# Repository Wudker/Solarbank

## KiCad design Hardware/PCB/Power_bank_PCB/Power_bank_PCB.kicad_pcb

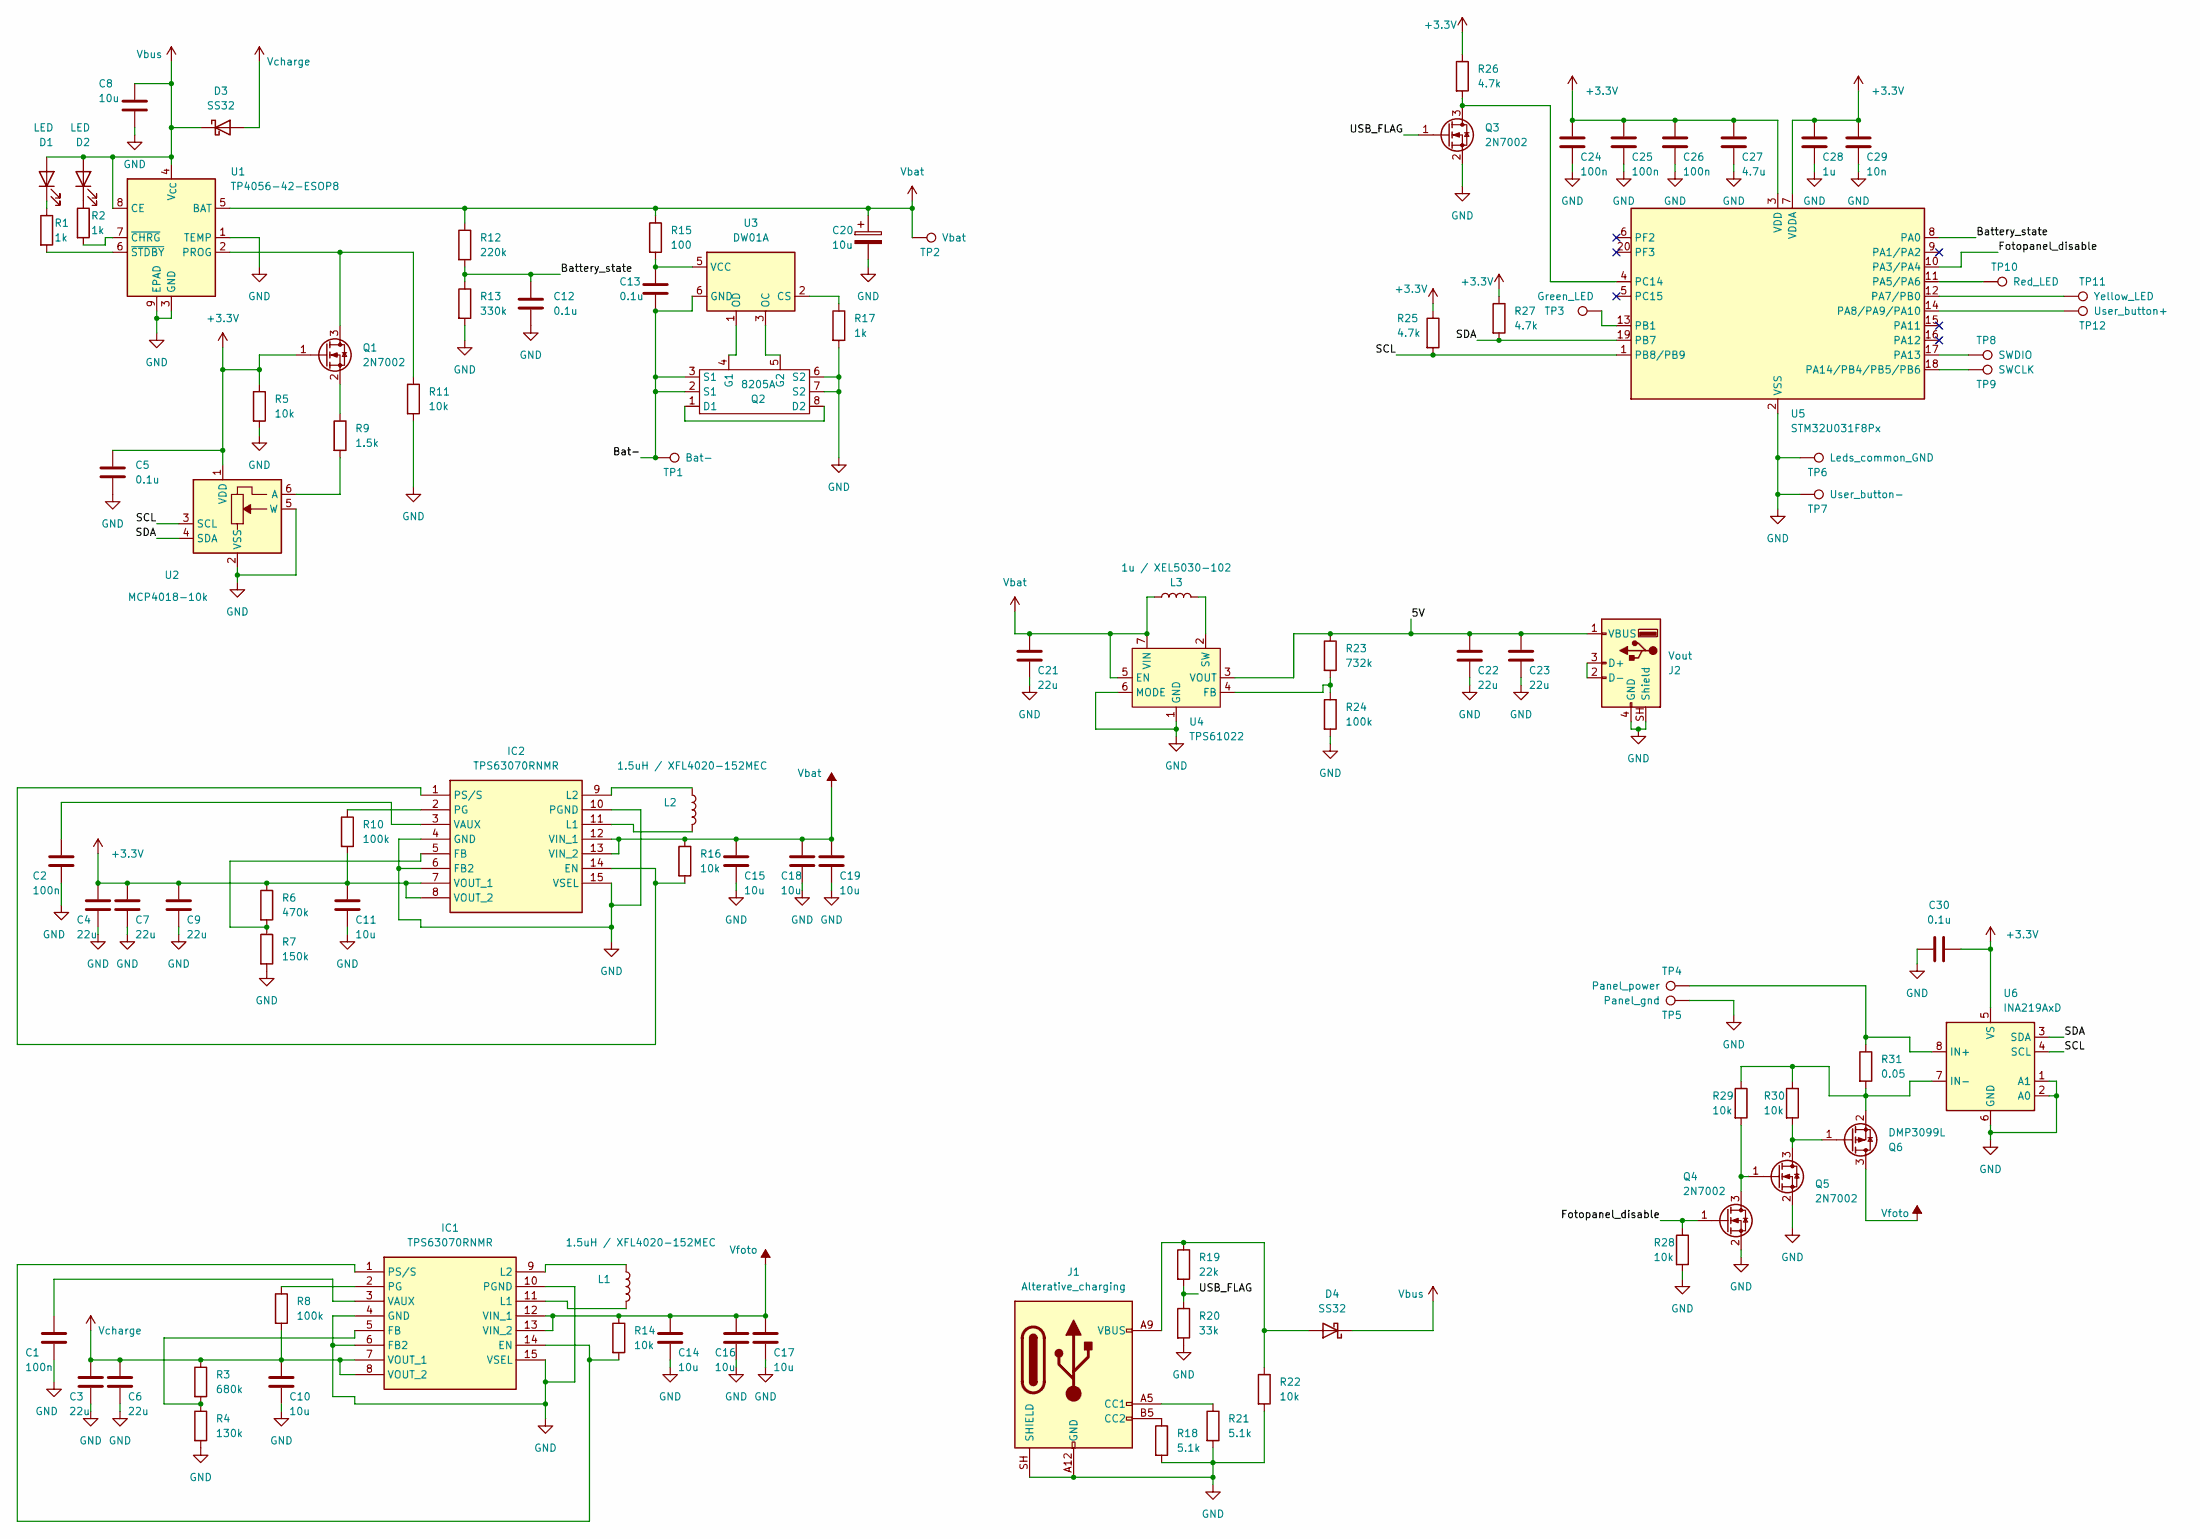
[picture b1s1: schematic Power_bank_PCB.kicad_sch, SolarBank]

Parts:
C1, C2, C24, C25, C26: 100n; C_1206_3216Metric
C3, C4, C6, C7, C9, C21, C22, C23: 22u; C_1206_3216Metric
C5, C12, C13, C30: 0.1u; C_1206_3216Metric
C8, C10, C11, C14, C15, C16, C17, C18, C19, C20: 10u; C_1206_3216Metric
C27: 4.7u; C_1206_3216Metric
C28: 1u; C_1206_3216Metric
C29: 10n; C_1206_3216Metric
D1, D2: LED; LED_1206_3216Metric_Pad1.42x1.75mm_HandSolder
D3, D4: SS32; D_SMA
IC1, IC2: TPS63070RNMR; TPS630701RNMR; Manufacturer_Part_Number TPS63070RNMR
J1: Alterative_charging; USB_C_Receptacle_GCT_USB4125-xx-x-0190_6P_TopMnt_Horizontal
J2: Vout; USB_A_Molex_67643_Horizontal
L1, L2: 1.5uH / XFL4020-152MEC; L_Coilcraft_XAL4020-XXX
L3: 1u / XEL5030-102; L_Coilcraft_XAL5030-XXX
Q1, Q3, Q4, Q5: 2N7002; SOT-23
Q2: 8205A; TSSOP-8_4.4x3mm_P0.65mm
Q6: DMP3099L; SOT-23
R1, R2, R17: 1k; R_1206_3216Metric
R3: 680k; R_1206_3216Metric
R4: 130k; R_1206_3216Metric
R5, R11, R14, R16, R22, R28, R29, R30: 10k; R_1206_3216Metric
R6: 470k; R_1206_3216Metric
R7: 150k; R_1206_3216Metric
R8, R10, R24: 100k; R_1206_3216Metric
R9: 1.5k; R_1206_3216Metric
R12: 220k; R_1206_3216Metric
R13: 330k; R_1206_3216Metric
R15: 100; R_1206_3216Metric
R18, R21: 5.1k; R_1206_3216Metric
R19: 22k; R_1206_3216Metric
R20: 33k; R_1206_3216Metric
R23: 732k; R_1206_3216Metric
R25, R26, R27: 4.7k; R_1206_3216Metric
R31: 0.05; R_1206_3216Metric
TP1: Bat-; TestPoint_Pad_D2.0mm
TP2: Vbat; TestPoint_Pad_D2.0mm
TP3: Green_LED; TestPoint_Pad_D2.0mm
TP4: Panel_power; TestPoint_Pad_D2.0mm
TP5: Panel_gnd; TestPoint_Pad_D2.0mm
TP6: Leds_common_GND; TestPoint_Pad_D2.0mm
TP7: User_button-; TestPoint_Pad_D2.0mm
TP8: SWDIO; TestPoint_Pad_D2.0mm
TP9: SWCLK; TestPoint_Pad_D2.0mm
TP10: Red_LED; TestPoint_Pad_D2.0mm
TP11: Yellow_LED; TestPoint_Pad_D2.0mm
TP12: User_button+; TestPoint_Pad_D2.0mm
U1: TP4056-42-ESOP8; SOIC-8-1EP_3.9x4.9mm_P1.27mm_EP2.41x3.3mm_ThermalVias
U2: MCP4018-10k; SOT-363_SC-70-6
U3: DW01A; SOT-23-6
U4: TPS61022; Texas_RWU0007A_VQFN-7_2x2mm_P0.5mm
U5: STM32U031F8Px; TSSOP-20_4.4x6.5mm_P0.65mm
U6: INA219AxD; SOIC-8_3.9x4.9mm_P1.27mm

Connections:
+3.3V: C4.2, C5.1, C7.2, C9.2, C11.2, C24.2, C25.2, C26.2, C27.2, C28.2, C29.2, C30.2, IC2.7 (VOUT_1), IC2.8 (VOUT_2), Q1.1 (G), R5.1, R6.1, R10.2, R25.1, R26.1, R27.1, U2.1 (VDD), U5.3 (VDD), U5.7 (VDDA), U6.5 (VS)
/5V: C22.2, C23.2, J2.1 (VBUS), R23.1, U4.3 (VOUT)
/Bat-: C13.1, Q2.2 (S1), Q2.3 (S1), TP1.1 (1_1), U3.6 (GND)
/Battery_state: C12.1, R12.2, R13.1, U5.8 (PA0)
/Fotopanel_disable: Q4.1 (G), R28.1, U5.10 (PA3/PA4)
/SCL: R25.2, U2.3 (SCL), U5.1 (PB8/PB9), U6.4 (SCL)
/SDA: R27.2, U2.4 (SDA), U5.19 (PB7), U6.3 (SDA)
/USB_FLAG: Q3.1 (G), R19.2, R20.1
GND: C1.1, C2.1, C3.1, C4.1, C5.2, C6.1, C7.1, C8.2, C9.1, C10.1, C11.1, C12.2, C14.1, C15.1, C16.1, C17.1, C18.1, C19.1, C20.2, C21.1, C22.1, C23.1, C24.1, C25.1, C26.1, C27.1, C28.1, C29.1, C30.1, IC1.4 (GND), IC1.6 (FB2), IC1.10 (PGND), IC1.15 (VSEL), IC2.4 (GND), IC2.6 (FB2), IC2.10 (PGND), IC2.15 (VSEL), J1.A12 (GND), J1.B12 (GND), J1.SH (SHIELD), J2.4 (GND), J2.SH (Shield), Q2.6 (S2), Q2.7 (S2), Q3.2 (S), Q4.2 (S), Q5.2 (S), R4.2, R5.2, R7.2, R11.2, R13.2, R17.2, R18.2, R20.2, R21.2, R22.2, R24.2, R28.2, TP5.1 (1_1), TP6.1 (1_1), TP7.1 (1_1), U1.1 (TEMP), U1.3 (GND), U1.9 (EPAD), U2.2 (VSS), U2.5 (W), U4.1 (GND), U4.6 (MODE), U5.2 (VSS), U6.1 (A1), U6.2 (A0), U6.6 (GND)
unnamed: D1.1 (K), R1.1
unnamed: D2.1 (K), R2.1
unnamed: D4.2 (A), J1.A9 (VBUS), J1.B9 (VBUS), R19.1, R22.1
unnamed: IC1.1 (PS/S), IC1.14 (EN), R14.2
unnamed: IC1.5 (FB), R3.2, R4.1
unnamed: IC1.11 (L1), L1.2
unnamed: IC1.9 (L2), L1.1
unnamed: IC1.2 (PG), R8.1
unnamed: C1.2, IC1.3 (VAUX)
unnamed: IC2.1 (PS/S), IC2.14 (EN), R16.2
unnamed: IC2.5 (FB), R6.2, R7.1
unnamed: IC2.11 (L1), L2.2
unnamed: IC2.9 (L2), L2.1
unnamed: IC2.2 (PG), R10.1
unnamed: C2.2, IC2.3 (VAUX)
unnamed: J1.A5 (CC1), R21.1
unnamed: J1.B5 (CC2), R18.1
unnamed: J2.2 (D-), J2.3 (D+)
unnamed: Q1.3 (D), R11.1, U1.2 (PROG)
unnamed: Q1.2 (S), R9.1
unnamed: Q2.1 (D1), Q2.8 (D2)
unnamed: Q2.4 (G1), U3.1 (OD)
unnamed: Q2.5 (G2), U3.3 (OC)
unnamed: Q3.3 (D), R26.2, U5.4 (PC14)
unnamed: Q4.3 (D), Q5.1 (G), R29.2
unnamed: Q5.3 (D), Q6.1 (G), R30.2
unnamed: Q6.2 (S), R29.1, R30.1, R31.2, U6.7 (IN-)
unnamed: R2.2, U1.7 (~CHRG)
unnamed: R1.2, U1.6 (~STDBY)
unnamed: R9.2, U2.6 (A)
unnamed: R17.1, U3.2 (CS)
unnamed: C13.2, R15.2, U3.5 (VCC)
unnamed: R23.2, R24.1, U4.4 (FB)
unnamed: L3.2, U4.2 (SW)
unnamed: TP10.1 (1_1), U5.11 (PA5/PA6)
unnamed: TP11.1 (1_1), U5.12 (PA7/PB0)
unnamed: TP12.1 (1_1), U5.14 (PA8/PA9/PA10)
unnamed: TP8.1 (1_1), U5.17 (PA13)
unnamed: TP9.1 (1_1), U5.18 (PA14/PB4/PB5/PB6)
unnamed: TP3.1 (1_1), U5.13 (PB1)
unnamed: R31.1, TP4.1 (1_1), U6.8 (IN+)
Vbat: C15.2, C18.2, C19.2, C20.1, C21.2, IC2.12 (VIN_1), IC2.13 (VIN_2), L3.1, R12.1, R15.1, R16.1, TP2.1 (1_1), U1.5 (BAT), U4.5 (EN), U4.7 (VIN)
Vbus: C8.1, D1.2 (A), D2.2 (A), D3.1 (K), D4.1 (K), U1.4 (V_{CC}), U1.8 (CE)
Vcharge: C3.2, C6.2, C10.2, D3.2 (A), IC1.7 (VOUT_1), IC1.8 (VOUT_2), R3.1, R8.2
Vfoto: C14.2, C16.2, C17.2, IC1.12 (VIN_1), IC1.13 (VIN_2), Q6.3 (D), R14.1

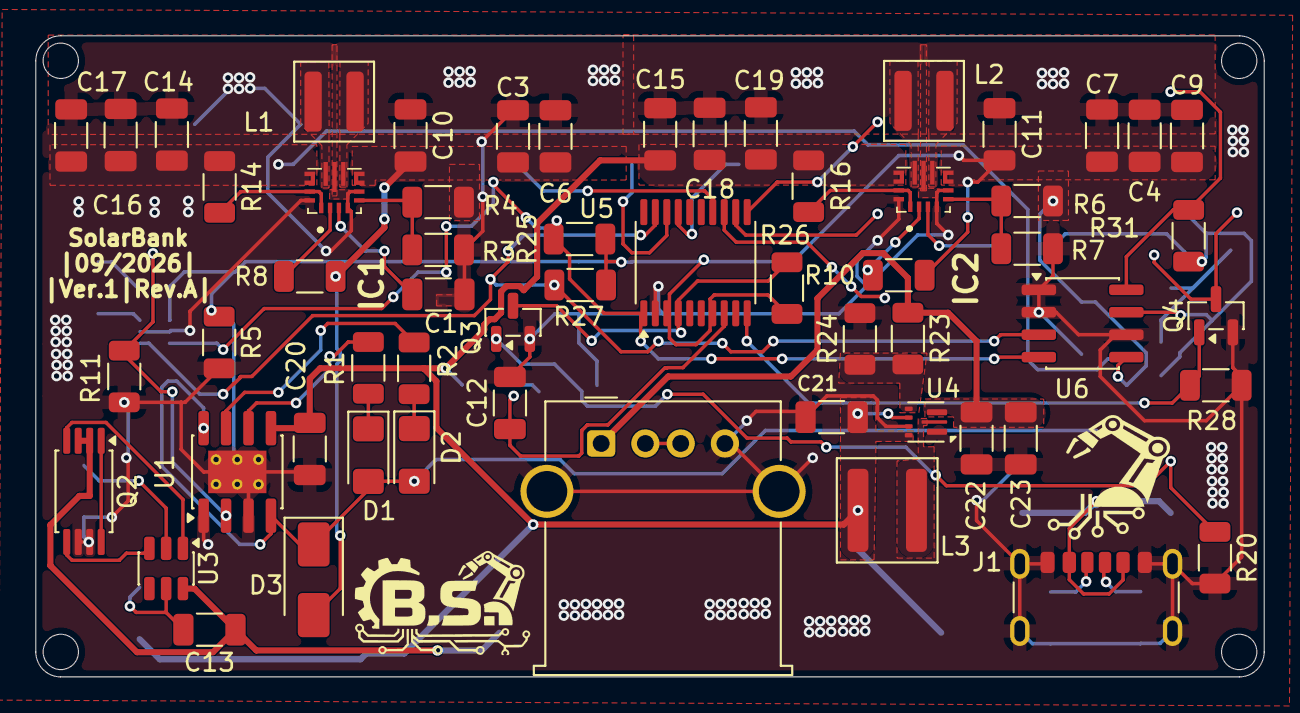
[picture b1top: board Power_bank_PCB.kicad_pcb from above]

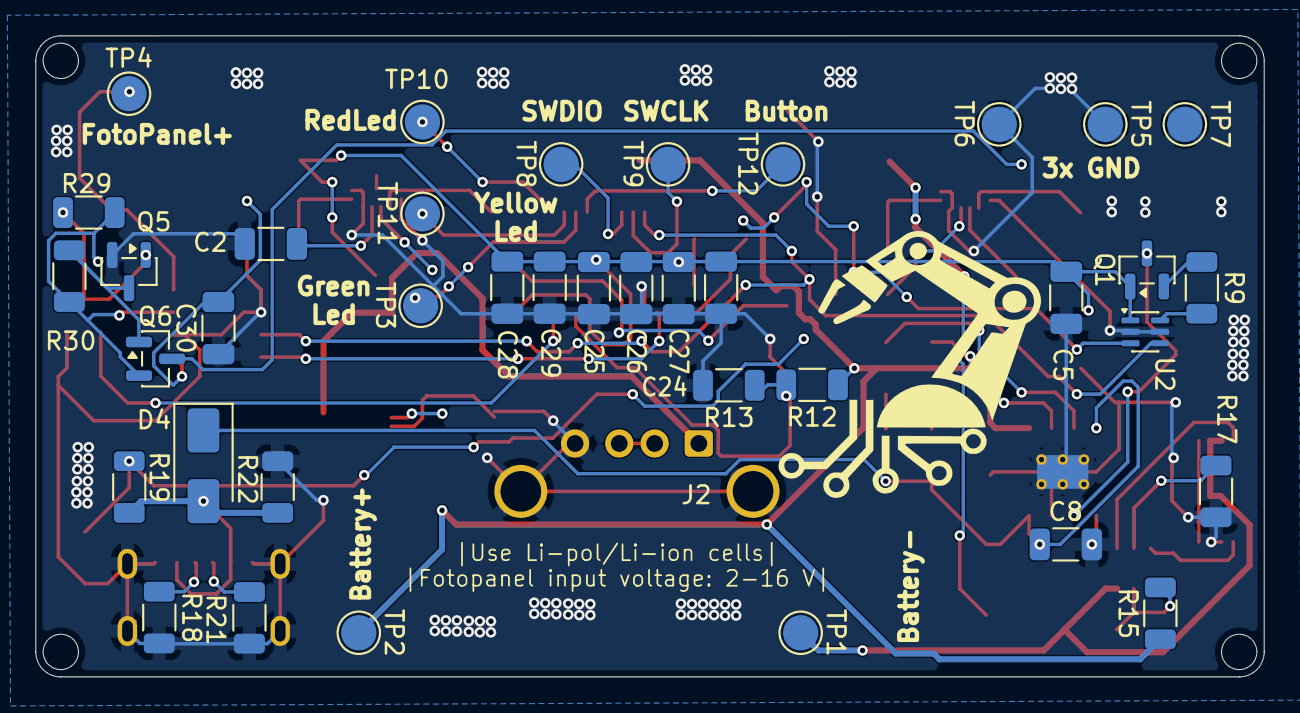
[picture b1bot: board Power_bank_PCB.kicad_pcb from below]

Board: 2 copper layers, 69.5 x 36.3 mm, 96 parts (38 on the bottom side), 54 nets.

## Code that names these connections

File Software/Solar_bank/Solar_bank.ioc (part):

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Mcu.Name=STM32U031F8Px
Mcu.Package=TSSOP20
Mcu.UserName=STM32U031F8Px
PA0-CK_IN.GPIOParameters=GPIO_Label
PA0-CK_IN.GPIO_Label=Battery_state
PA0-CK_IN.Mode=IN4
PA0-CK_IN.Signal=ADC1_IN4
PA13\ (SWDIO).Mode=Serial_Wire
PA13\ (SWDIO).Signal=DEBUG_JTMS-SWDIO
PA14\ (SWCLK).Mode=Serial_Wire
PA14\ (SWCLK).Signal=DEBUG_JTCK-SWCLK
PA14\ (SWCLK)__PB4__PB5__PB6.StandardMode=true
PA1__PA2.StandardMode=true
PA3.GPIOParameters=GPIO_Label
PA3.GPIO_Label=Fotopanel_enable
PA3.Signal=GPIO_Output
PA3__PA4.StandardMode=true
PA5__PA6.StandardMode=true
PA6.GPIOParameters=GPIO_Label
PA6.GPIO_Label=LED_status_red
PA6.Signal=GPIO_Output
PA7.GPIOParameters=GPIO_Label
PA7.GPIO_Label=LED_status_orange
PA7.Signal=GPIO_Output
PA7__PB0.StandardMode=true
PA8.GPIOParameters=GPIO_Label
PA8.GPIO_Label=User_button_input
PA8.Signal=GPXTI8
PB1.GPIOParameters=GPIO_Label
PB1.GPIO_Label=LED_status_green
PB1.Signal=GPIO_Output
PB7.Mode=I2C
PB7.Signal=I2C1_SDA
PB8.Mode=I2C
PB8.Signal=I2C1_SCL
PB8__PB9.StandardMode=true
PC14-OSC32_IN.GPIOParameters=GPIO_Label
PC14-OSC32_IN.GPIO_Label=USB_input
PC14-OSC32_IN.Signal=GPIO_Input
RCC.HSE_VALUE=4000000
RCC.SYSCLKFreq_VALUE=16000000
board=custom
